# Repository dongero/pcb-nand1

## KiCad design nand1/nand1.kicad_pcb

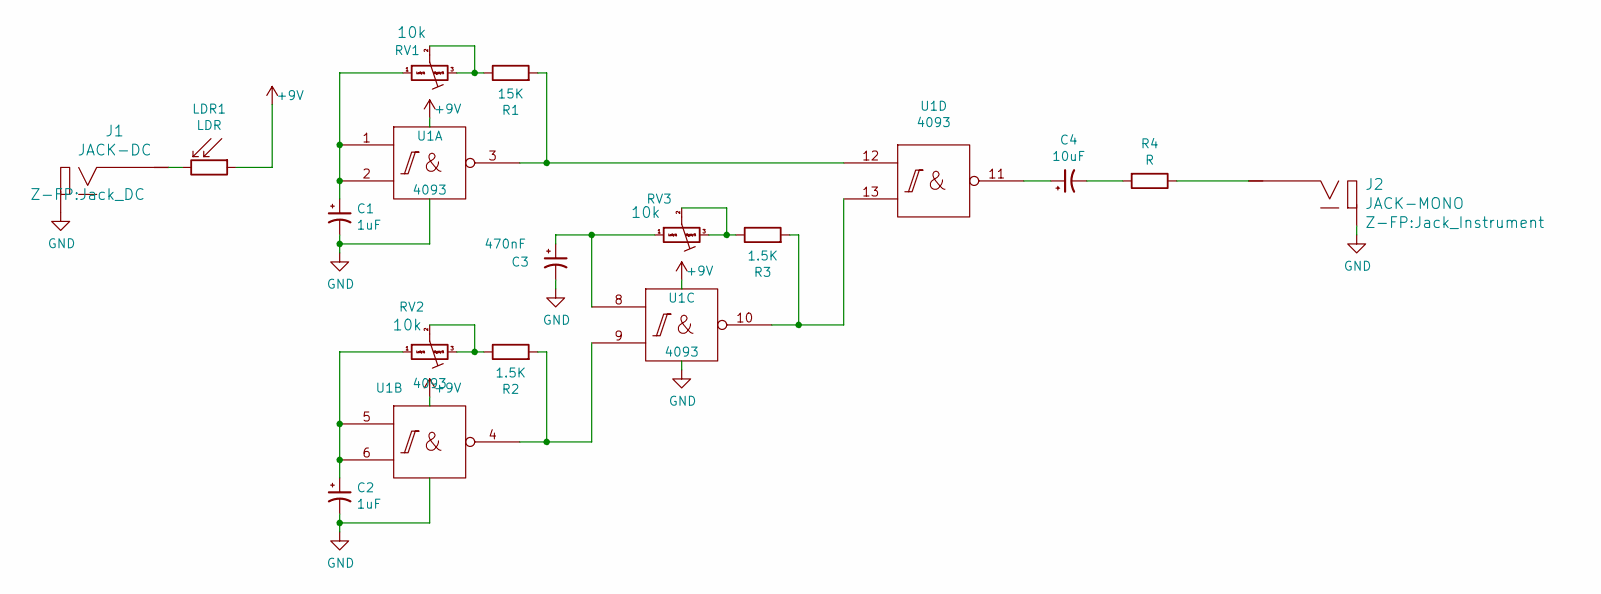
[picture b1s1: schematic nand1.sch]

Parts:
C1, C2: 1uF; CP_Radial_P2.5mm
C3: 470nF; CP_Radial_P2.5mm
C4: 10uF; CP_Radial_P2.5mm
J1: JACK-DC; Jack_DC
J2: JACK-MONO; Jack_Instrument
LDR1: LDR; Jack_Instrument
R1: 15K; R_Axial_DIN0207_L6.3mm_D2.5mm_P7.62mm_Horizontal
R2, R3: 1.5K; R_Axial_DIN0207_L6.3mm_D2.5mm_P7.62mm_Horizontal
R4: R; R_Axial_DIN0207_L6.3mm_D2.5mm_P7.62mm_Horizontal
RV1, RV2, RV3: TrimPot_T73YEt_10k; Pot_Trim_7x6.6mm_T73YE; Part Number T73YE103KT20
U1: 4093; DIP-14_W7.62mm

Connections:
+9V: LDR1.1, U1.14 (Vdd)
GND: C1.2, C2.2, C3.2, J1.2 (GND), J2.2 (GND), U1.7 (Vss)
unnamed: C1.1, RV1.1 (Left), U1.1, U1.2
unnamed: C2.1, RV2.1 (Left), U1.5, U1.6
unnamed: C3.1, RV3.1 (Left), U1.8
unnamed: C4.1, U1.11
unnamed: C4.2, R4.2
unnamed: J1.1 (V), LDR1.2
unnamed: J2.1 (V), R4.1
unnamed: R1.1, RV1.2 (Center), RV1.3 (Right)
unnamed: R1.2, U1.3, U1.12
unnamed: R2.1, RV2.2 (Center), RV2.3 (Right)
unnamed: R2.2, U1.4, U1.9
unnamed: R3.1, RV3.2 (Center), RV3.3 (Right)
unnamed: R3.2, U1.10, U1.13

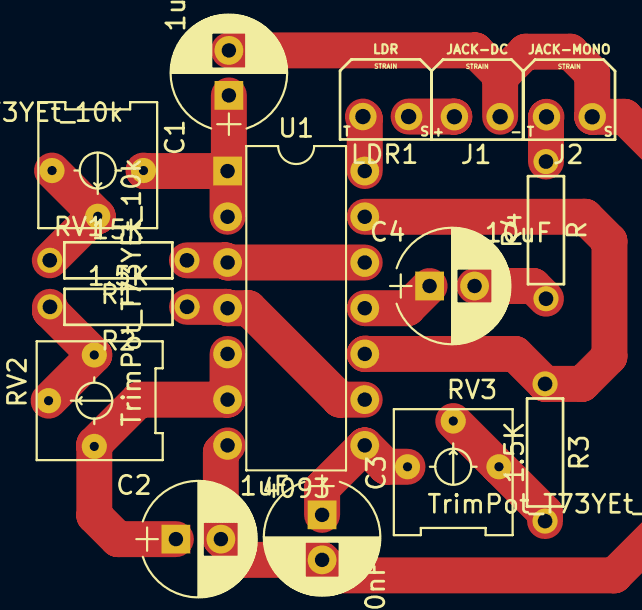
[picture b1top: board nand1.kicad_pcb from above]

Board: 2 copper layers, 15 parts (0 on the bottom side), 15 nets.

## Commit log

2020-03-05 started pcb
2021-02-10 Made pcblayout for etching
